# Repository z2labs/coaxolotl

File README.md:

# Coaxolotl

**A mast-head LNA and 8-way filter bank that lives entirely on one coax.**
An RTL-SDR's bias-T powers it, and the same bias-T switches it by blinking
its power in short gaps. It answers on the same coax with a keyed clock the
dongle receives, so the host sees what it did and what it measures. Its
front panel shows every internal state on a lamp, like a 1970s
minicomputer.

```
  BANK   ○THRU ○LF ○160/80 ○60-30 ○20-10 ○6/4m ●2m/AIR ○70/23cm
  FRAME  S:●○●  P:●●○●○○  C:○○●○●●
  DECODE ○RX ○0 ○1 ●OK ○ERR  | ○SYNC ○CHK ○GAP ○RUNT ○TMO
  RF     ●LNA ○BYP ○AUTO ●FMN  | ○I-LO ●I-OK ○I-HI ○TRIP
  SYSTEM ○RUN ●HOLD ○LOW ○QUIET  | ○DROP ○GLT ○RST
```

## How it works

```mermaid
flowchart LR
  PC[host<br/>coaxolotl.py · SDR++] -- USB --> RTL[RTL-SDR V3<br/>bias-T 4.5 V]
  RTL <== "RF + replies ↑ · DC + OOK gaps ↓" ==> BOX
  subgraph BOX[Coaxolotl box]
    direction TB
    DEC[EFM8BB2<br/>gap decoder] --> SW[LNA / bypass<br/>8x filter bank]
    DEC --> PANEL[48+1 lamps]
    SCAP[0.1 F hold-up] -.-> DEC
  end
  ANT[antenna] --> BOX
```

* **Link.** Bias off for 30 ms is a 0 and for 70 ms is a 1, with 100 ms of
  power between bits. A frame is `sync 101 | bank·LNA·quiet·clr | inverse`
  and takes about 2.5 s. The sync bits calibrate the threshold, so clock
  skew, slow discharge and USB jitter cancel out.
  → [docs/protocol.md](docs/protocol.md)
* **Back-channel.** After every frame (and once after boot) the MCU keys a
  12.25 MHz clock onto the coax for 0.8 s. The dongle hears its 3rd
  harmonic at 36.75 MHz. The 8-byte Manchester packet carries ACK/NAK with
  the error, the switch state actually set, VCOAX, the whole coax current
  (the bias-T budget, BUDGET flag at 170 mA), LNA current, supercap voltage
  and the sticky flags. Readings are calibrated against a meter over the same
  link. The host searches the band for it, so the ±2 % RC oscillator needs no
  trimming.
  → [docs/protocol.md](docs/protocol.md#back-channel-box--host)
* **SDR++.** `sdrpp/coaxolotl_source` is an RTL-SDR source for SDR++ with
  the link built in: branch, LNA, Send/Poll/Clear, follow-tuning and a
  telemetry readout. → [sdrpp/README.md](sdrpp/README.md)
* **RF path.** Antenna → protection → LNA (with preselector, optional FM
  notch) or bypass → PE42582 SP8T → 8 filters → PE42582 → bias-T → coax.
  The HF/LF branches force bypass automatically.
  → [bandplan.json](bandplan.json)
* **Power.**
  * An ideal diode keeps the sense node fast.
  * A 330 µF stage boots the MCU in about 30 ms, and a 0.1 F supercap rides
    through dropouts for minutes.
  * The LNA sits behind a current-limited switch with a shunt monitor.
  → [docs/hardware.md](docs/hardware.md)
* **Quiet when idle.** The EFM8BB2 Snoozes with its high-frequency clock
  stopped. It wakes only on a bias edge, an LNA fault or every 6.5 s for
  housekeeping. The lamps are statically latched, so there is no
  multiplexing noise either. The RUN lamp tells you when the MCU clock is
  running.
* **Panel.** 48 lamps on 6×74HC595 plus a hard-wired PWR lamp. It shows bank,
  received bits, decoder errors, LNA path and current, trip, hold-up, rail
  voltage and sticky dropout/glitch/reset flags. Software modes: full, bands
  only, or off (PWR lamp only), kept in flash. → [docs/panel.md](docs/panel.md)

## Quick start

```bash
# host tests + simulator (gcc, g++, python3 + numpy)
make -C firmware test sim
make -C sdrpp test
python3 -m unittest discover -s host

# what the box would do, without hardware
python3 host/coaxolotl.py send --band 2m --lna --backend dry-run \
  | firmware/build/sim --fall-delay 6 --jitter 2

# firmware (SDCC >= 4.2)
make -C firmware            # EFM8BB52 (control board), Snooze build
make -C firmware SNOOZE=0   # bring-up build, classic registers only
make -C firmware MCU=bb21   # EFM8BB21 QFN20: the 4-layer RF board

# real link
python3 host/coaxolotl.py bands
python3 host/coaxolotl.py send --band 2m --lna                 # pyrtlsdr
python3 host/coaxolotl.py send --bank 3 --backend rtl_biast    # rtl-sdr-blog tool
python3 host/coaxolotl.py panel bands                          # lamps: full | bands | off
python3 host/coaxolotl.py send --band 2m --lna --listen        # ... and read the reply
python3 host/coaxolotl_gui.py                                  # control panel (--sim: no hardware)
```

## Pin map

### EFM8BB52F32I-C-QFN32: control board (`make -C firmware`, the default)

Source of truth: `firmware/src/hal_efm8bb52.c`; checked against the
`hardware/kicad_ctrl` netlist.

| Pin | Port | Net | Dir | Function |
|---|---|---|---|---|
| 1 | P0.0 | VREF | ana | precision reference 2.4 V, C50 100 nF; on only while measuring |
| 32 | P0.1 | FAULT_N | in | TPS2553 FAULT, 100 k pull-up; port-match wake |
| 31 | P0.2 | SENSE | in + ana | VCOAX divider 11k/22k: port-match wake on both edges and ADC0.0 at once (PRTDRV.COEX); C2 10 nF |
| 30 | P0.3 | SCAP_ADC | ana | supercap / 2 (1 M / 1 M, C11), ADC0.1 |
| 29 | P0.4 | TP_TX | out | UART0 TX test point (factory bootloader, debug) |
| 28 | P0.5 | TP_RX | in | UART0 RX test point |
| 27 | P0.6 | LNA_EN | out | TPS2553 EN; 10 k pull-down |
| 26 | P0.7 | LNA_PATH | out | input SPDT U6, 1 = LNA; 10 k pull-down = bypass |
| 25, 24, 23 | P1.0–P1.2 | SW_V1..V3 | out | both PE42582 (via J6); 10 k pull-downs = F0 THRU |
| 22 | P1.3 | LNA_PATH_OUT | out | output SPDT U7, same polarity; 10 k pull-down |
| 21 | P1.4 | FMN | out | FM notch SPDTs; 10 k pull-down |
| 20, 19 | P1.5, P1.6 | — | out | spare, driven low |
| 18 | P1.7 | BEACON | out | PCA CEX0 12.25 MHz during a reply → R31/R32/R33/C47 → coax; low otherwise |
| 17 | P2.0 | LED_SER | out | 74HC595 chain data (U14 first) |
| 16 | P2.1 | LED_SCK | out | shift clock |
| 15 | P2.2 | LED_RCK | out | latch clock |
| 14 | P2.3 | LED_OE_N | out | output enable; 10 k pull-up = lamps dark in reset |
| 13 | P2.4 | ILNA_ADC | ana | LNA current: R7 0.39 Ω, U3 INA180A2, 19.5 mV/mA, R8/C7; ADC0.13 |
| 12 | P2.5 | ITOT_ADC | ana | whole coax current: R35 0.1 Ω, U20 INA180A3, 10 mV/mA, R36/C48; ADC0.14 |
| 11 | P2.6 | — | out | spare, driven low |
| 10–6 | P3.0–P3.4 | — | out | spare, driven low |
| 5 | P3.7 / C2D | C2D | | debug; R34 10 k pull-up (low at reset = factory bootloader) |
| 4 | RSTb / C2CK | RST_N | | R13 10 k pull-up, C2 clock |
| 3 | VDD | +3V3 | | C15 100 nF + C14 1 µF |
| 2 | N/C | | | |
| EP | GND | | | the only ground pin |

J6 (via row to a later RF board): 1 +3V3, 2 LNA_VCC, 3–5 SW_V1..V3,
6 LNA_PATH, 7 LNA_PATH_OUT, 8 FMN, 9–10 GND.

### EFM8BB21F16G-C-QFN20: 4-layer RF board (`make -C firmware MCU=bb21`)

Source of truth: `firmware/src/hal_efm8bb2.c`. All 16 port pins are used.

| Pin | Port | Net | Dir | Function |
|---|---|---|---|---|
| 2 | P0.0 | SENSE | in | VCOAX divider; port-match wake |
| 1 | P0.1 | VC_ADC | ana | same divider node |
| 20 | P0.2 | SCAP_ADC | ana | supercap / 2 |
| 19 | P0.3 | ILNA_ADC | ana | INA180A2 output |
| 18 | P0.4 | LED_OE_N | out | lamp output enable; 10 k pull-up |
| 17 | P0.5 | FAULT_N | in | TPS2553 FAULT; port-match wake |
| 16 | P0.6 | LNA_EN | out | 10 k pull-down |
| 15 | P0.7 | LNA_PATH | out | input SPDT U6; 10 k pull-down |
| 14, 13, 11 | P1.0–P1.2 | SW_V1..V3 | out | both PE42582; 10 k pull-downs |
| 10 | P1.3 | LNA_PATH_OUT | out | output SPDT U7; 10 k pull-down |
| 9 | P1.4 | LED_SER (+ BEACON) | out | 595 data; PCA CEX0 during a reply (no tap on this board yet) |
| 8 | P1.5 | LED_SCK | out | |
| 7 | P1.6 | LED_RCK | out | |
| 6 | P2.0 / C2D | FMN | out | through R30 1 k; 10 k pull-down |
| 5 | RSTb / C2CK | RST_N | | 10 k pull-up |
| 4 | VDD | +3V3 | | |
| 3, 12, EP | GND | | | |

No whole-coax current monitor on this board: I_TOT reads 0.

## Repository

| Path | What |
|---|---|
| `bandplan.json` | the 8 branches, single source of truth (firmware header is generated) |
| `firmware/src/decoder.*` | gap-width OOK decoder, pure C |
| `firmware/src/app.*` | RF routing, health, sticky flags, animations, pure C |
| `firmware/src/panel.*` | state → 48-bit lamp image |
| `firmware/src/beacon.*` | reply packet, CRC and chip sequence, pure C |
| `firmware/src/hal_efm8bb2.c`, `main.c` | EFM8BB21 (QFN20) hardware layer and main loop |
| `firmware/src/hal_efm8bb52.c` | EFM8BB52F32 (QFN32) hardware layer, the default build |
| `firmware/include/efm8bb*_sfr.h` | minimal SDCC SFR maps (BB2, BB52) |
| `firmware/test/` | unit tests and `sim` (edge replay + ASCII panel) |
| `host/coaxolotl.py` | keyer: pyrtlsdr / rtl_biast / dry-run, `--listen`, `listen`, `decode` |
| `host/backchannel.py` | reply packet and demodulator (numpy) |
| `host/link.py` | one open RTL-SDR (or the firmware simulator): key a frame, read the reply |
| `host/coaxolotl_gui.py` | control panel for the PC (tkinter), see `docs/host.md` |
| `sdrpp/` | SDR++ source module and its standalone tests |
| `hardware/kicad/` | 4-layer RF board: generated schematic (`tools/build.py`), layout, JLC package in `jlc/` |
| `hardware/kicad_ctrl/` | 2-layer control board without RF (`COAX_VARIANT=ctrl`), JLC package in `jlc/` |
| `hardware/bom.csv` | grouped BOM of the RF board schematic (`tools/bom.py`) |
| `docs/` | protocol, hardware, panel, bring-up, PC software (`host.md`) |

## Status (v0.1)

* ✅ Decoder, app logic and panel pass 194 host checks. That includes all 64
  payloads, 1800 randomised frames at ±10 % clock skew, 0–10 ms fall delay
  and ±3 ms jitter, every error path and the LED power budget.
* ✅ Host encoder → firmware decoder, end to end, through the simulator.
* ✅ The firmware builds with SDCC 4.2, back-channel included, in both the
  Snooze and the bring-up build: EFM8BB52F32 about 15.4 of 28 kB, EFM8BB21F16G
  about 15.2 of 15.4 kB (full: new features go to the BB52 only). One flash
  page holds the settings log (panel mode, calibration).
* ✅ PC control panel (`host/coaxolotl_gui.py`) and link layer (`host/link.py`),
  tested end to end against the firmware simulator.
* ✅ Back-channel: firmware checks for HELLO/ACK/NAK, timing, contents and
  the chip round-trip. Firmware packets go through the simulator into the
  Python and C++ demodulators, which decode synthetic captures with the
  carrier anywhere in ±0.75 MHz and chips ±10 %.
* ⚠️ The SDR++ module compiles against the SDR++ headers but has not run in
  SDR++ yet. The beacon level (about −65 dBm) is calculated, not measured.
* ⚠️ The firmware has **not run on silicon yet**. Three EFM8BB2 register
  details (Snooze bit, Timer 4 LFOSC clock select, Snooze wake on a Timer 4
  wrap), the ADC setup and the PCA/CLKSEL/crossbar setup of the beacon are
  marked VERIFY. `docs/bringup.md` has a test
  for each, and the `SNOOZE=0` build avoids them.
* ✅ Schematic and two routed layouts with JLC packages: the 4-layer RF board
  (`hardware/kicad`) and the 2-layer control board without RF
  (`hardware/kicad_ctrl`). Open items are listed in `docs/hardware.md`.

## License

| Part | License |
|---|---|
| Hardware: `hardware/` (schematics, PCB, BOM), and the hardware design in `docs/hardware.md` | [CERN-OHL-S-2.0](hardware/LICENSE) |
| Software: `firmware/`, `host/`, `tools/`, future SDR plugins | [MIT](LICENSE) |

Documentation follows the part it describes.

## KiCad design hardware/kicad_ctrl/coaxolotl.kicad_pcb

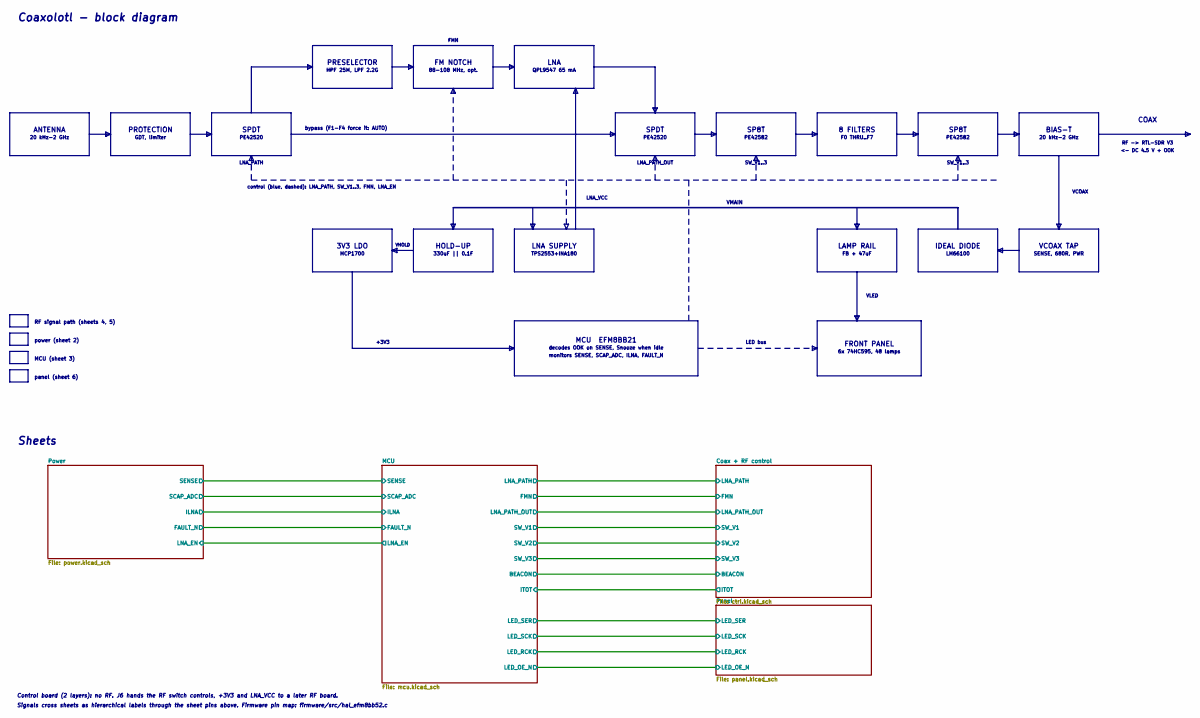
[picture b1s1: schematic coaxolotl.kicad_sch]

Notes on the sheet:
Coaxolotl - block diagram
ANTENNA
20 kHz-2 GHz
PROTECTION
GDT, limiter
SPDT
PE42520
SP8T
PE42582
8 FILTERS
F0 THRU..F7
BIAS-T
PRESELECTOR
HPF 25M, LPF 2.2G
FM NOTCH
88-108 MHz, opt.
LNA
QPL9547 65 mA
bypass (F1-F4 force it: AUTO)
COAX
RF -> RTL-SDR V3
<- DC 4.5 V + OOK
LNA_PATH
LNA_PATH_OUT
SW_V1..3
FMN
VCOAX TAP
SENSE, 680R, PWR
IDEAL DIODE
LM66100
LAMP RAIL
FB + 47uF
LNA SUPPLY
TPS2553+INA180
HOLD-UP
330uF || 0.1F
3V3 LDO
MCP1700
VCOAX
VMAIN

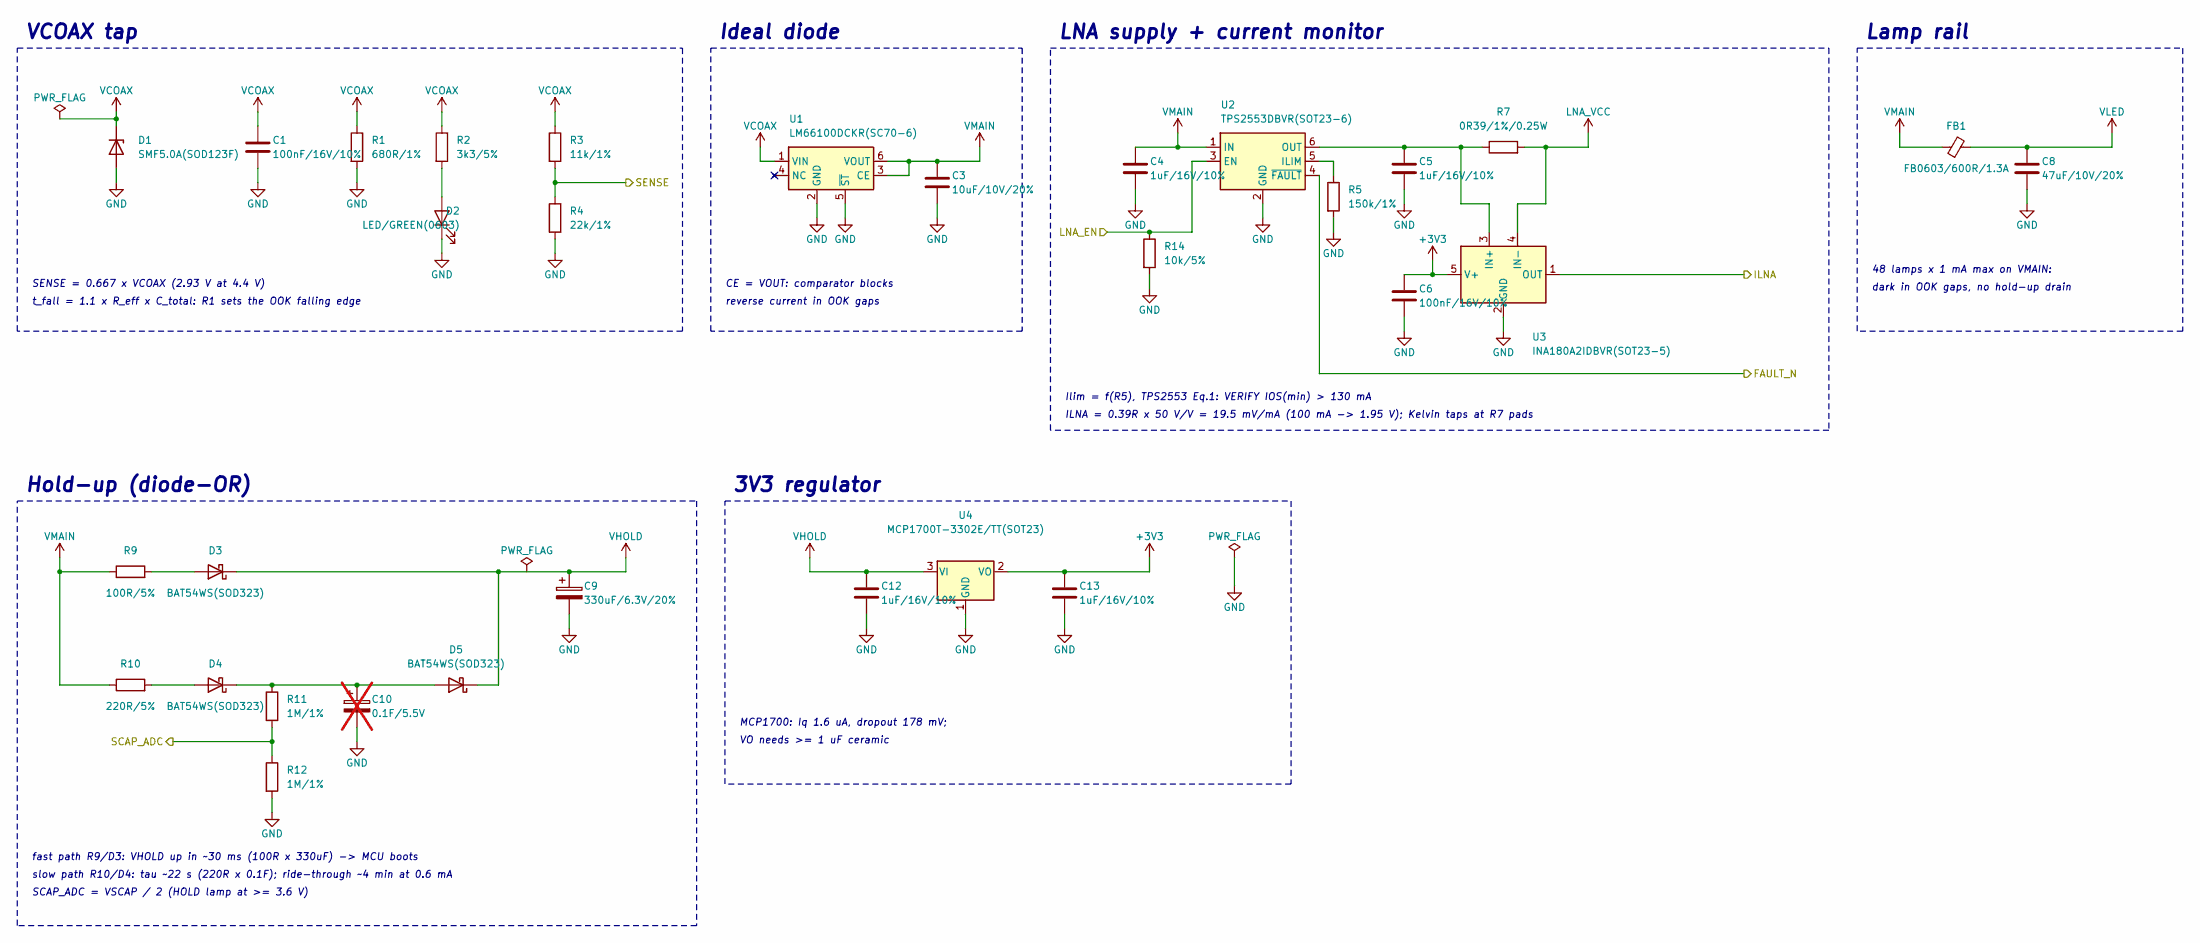
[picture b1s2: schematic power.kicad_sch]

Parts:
C1, C6: 100nF/16V/10%; C_0603_1608Metric
C3: 10uF/10V/20%; C_0805_2012Metric
C4, C5, C12, C13: 1uF/16V/10%; C_0603_1608Metric
C8: 47uF/10V/20%; C_1206_3216Metric
C9: 330uF/6.3V/20%; CP_EIA-7343-31_Kemet-D; MPN T520D337M006ATE025
C10: 0.1F/5.5V; CP_Radial_D13.0mm_P5.00mm; MPN KR-5R5V104-R; not fitted
D1: SMF5.0A(SOD123F); D_SOD-123F
D2: LED/GREEN(0603); LED_0603_1608Metric
D3, D4, D5: BAT54WS(SOD323); D_SOD-323
FB1: FB0603/600R/1.3A; L_0603_1608Metric; MPN BLM18KG601SN1D
R1: 680R/1%; R_0603_1608Metric
R2: 3k3/5%; R_0603_1608Metric
R3: 11k/1%; R_0603_1608Metric
R4: 22k/1%; R_0603_1608Metric
R5: 150k/1%; R_0603_1608Metric
R7: 0R39/1%/0.25W; R_1206_3216Metric; MPN ERJ-8BQFR39V
R9: 100R/5%; R_0603_1608Metric
R10: 220R/5%; R_0603_1608Metric
R11, R12: 1M/1%; R_0603_1608Metric
R14: 10k/5%; R_0603_1608Metric
U1: LM66100DCKR(SC70-6); SOT-363_SC-70-6
U2: TPS2553DBVR(SOT23-6); SOT-23-6
U3: INA180A2IDBVR(SOT23-5); SOT-23-5
U4: MCP1700T-3302E/TT(SOT23); SOT-23

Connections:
+3V3: C6.1, C13.1, U3.5 (V+), U4.2 (VO); also elsewhere on the board
/MCU/FAULT_N: U2.4 (~FAULT); also elsewhere on the board
/MCU/ILNA: U3.1 (OUT); also elsewhere on the board
/MCU/LNA_EN: R14.1, U2.3 (EN); also elsewhere on the board
/MCU/SCAP_ADC: R11.2, R12.1; also elsewhere on the board
/MCU/SENSE: R3.2, R4.1; also elsewhere on the board
GND: C1.2, C3.2, C4.2, C5.2, C6.2, C8.2, C9.2, C10.2, C12.2, C13.2, D1.2 (A), D2.1 (K), R1.2, R4.2, R5.2, R12.2, R14.2, U1.2 (GND), U1.5 (~ST), U2.2 (GND), U3.2 (GND), U4.1 (GND); also elsewhere on the board
LNA_VCC: R7.2, U3.4 (IN-); also elsewhere on the board
unnamed: D2.2 (A), R2.2
unnamed: D3.2 (A), R9.2
unnamed: D4.2 (A), R10.2
unnamed: C10.1, D4.1 (K), D5.2 (A), R11.1
unnamed: R5.1, U2.5 (ILIM)
unnamed: C5.1, R7.1, U2.6 (OUT), U3.3 (IN+)
VCOAX: C1.1, D1.1 (K), R1.1, R2.1, R3.1, U1.1 (VIN); also elsewhere on the board
VHOLD: C9.1, C12.1, D3.1 (K), D5.1 (K), U4.3 (VI)
VLED: C8.1, FB1.2; also elsewhere on the board
VMAIN: C3.1, C4.1, FB1.1, R9.1, R10.1, U1.3 (CE), U1.6 (VOUT), U2.1 (IN)

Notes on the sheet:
VCOAX tap
SENSE = 0.667 x VCOAX (2.93 V at 4.4 V)
t_fall = 1.1 x R_eff x C_total: R1 sets the OOK falling edge
Ideal diode
CE = VOUT: comparator blocks
reverse current in OOK gaps
LNA supply + current monitor
Ilim = f(R5), TPS2553 Eq.1: VERIFY IOS(min) > 130 mA
ILNA = 0.39R x 50 V/V = 19.5 mV/mA (100 mA -> 1.95 V); Kelvin taps at R7 pads
Lamp rail
48 lamps x 1 mA max on VMAIN:
dark in OOK gaps, no hold-up drain
Hold-up (diode-OR)
fast path R9/D3: VHOLD up in ~30 ms (100R x 330uF) -> MCU boots
slow path R10/D4: tau ~22 s (220R x 0.1F); ride-through ~4 min at 0.6 mA
SCAP_ADC = VSCAP / 2 (HOLD lamp at >= 3.6 V)
3V3 regulator
MCP1700: Iq 1.6 uA, dropout 178 mV;
VO needs >= 1 uF ceramic

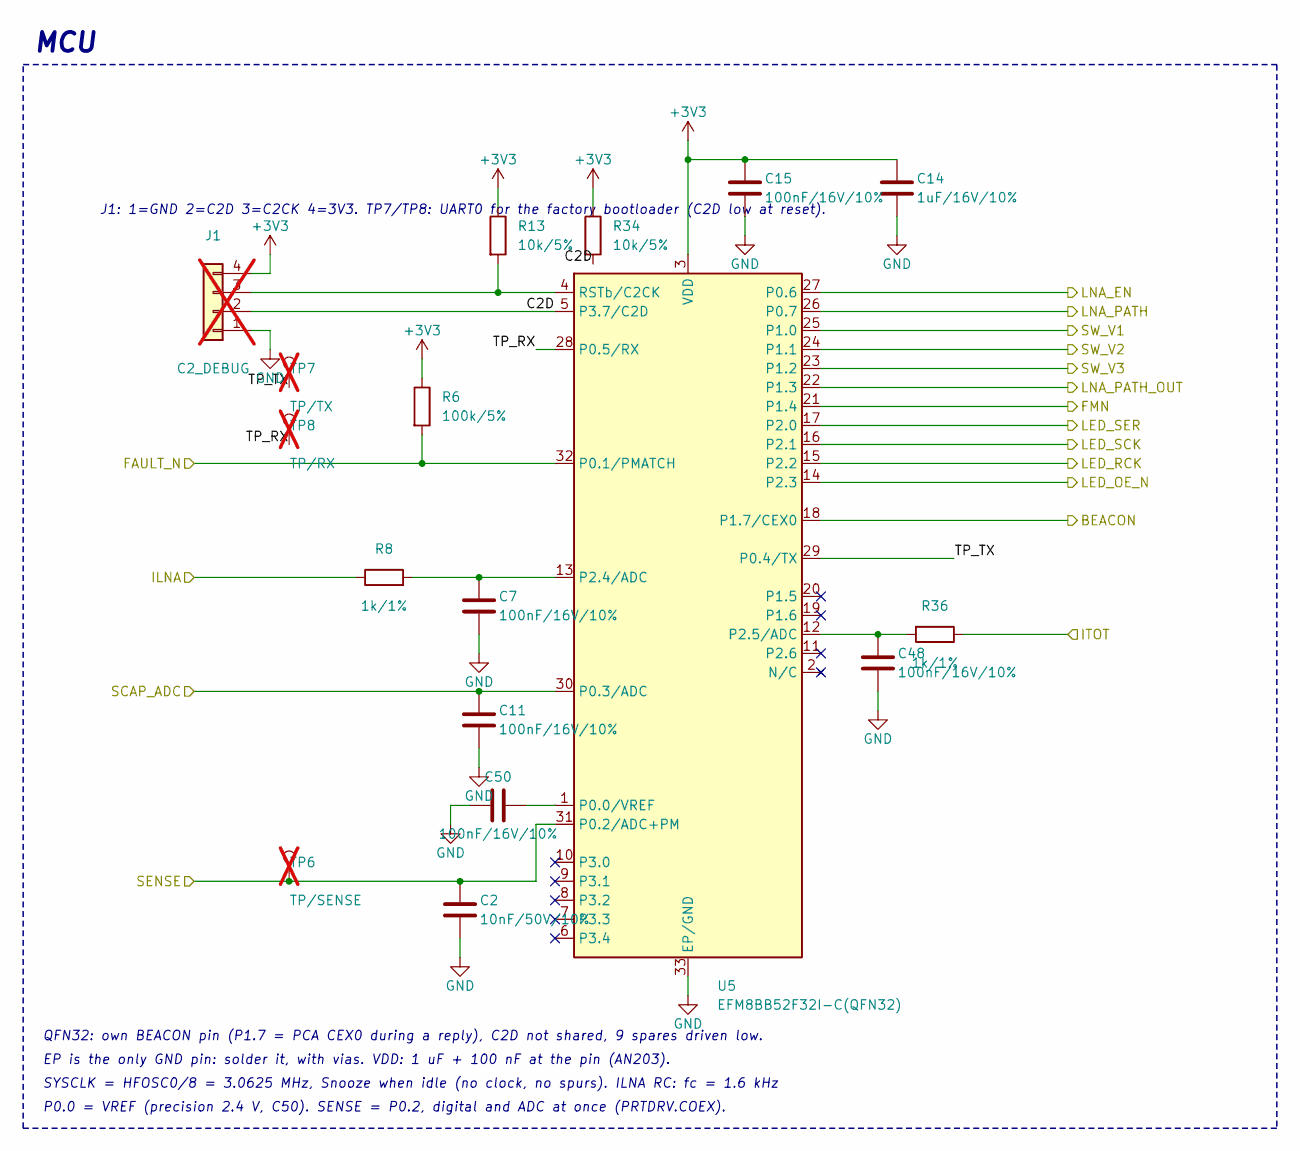
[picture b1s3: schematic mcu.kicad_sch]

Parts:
C2: 10nF/50V/10%; C_0603_1608Metric
C7, C11, C15, C48, C50: 100nF/16V/10%; C_0603_1608Metric
C14: 1uF/16V/10%; C_0603_1608Metric
J1: C2_DEBUG; PinHeader_1x04_P2.54mm_Vertical; not fitted
R6: 100k/5%; R_0603_1608Metric
R8, R36: 1k/1%; R_0603_1608Metric
R13, R34: 10k/5%; R_0603_1608Metric
TP6: TP/SENSE; TestPoint_Pad_D1.0mm; not fitted
TP7: TP/TX; TestPoint_Pad_D1.0mm; not fitted
TP8: TP/RX; TestPoint_Pad_D1.0mm; not fitted
U5: EFM8BB52F32I-C(QFN32); QFN-32-1EP_5x5mm_P0.5mm_EP3.45x3.45mm

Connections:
+3V3: C14.1, C15.1, J1.4, R6.1, R13.1, R34.1, U5.3 (VDD); also elsewhere on the board
/Coax + RF control/BEACON: U5.18 (P1.7/CEX0); also elsewhere on the board
/Coax + RF control/FMN: U5.21 (P1.4); also elsewhere on the board
/Coax + RF control/ITOT: R36.1; also elsewhere on the board
/Coax + RF control/LNA_PATH: U5.26 (P0.7); also elsewhere on the board
/Coax + RF control/LNA_PATH_OUT: U5.22 (P1.3); also elsewhere on the board
/Coax + RF control/SW_V1: U5.25 (P1.0); also elsewhere on the board
/Coax + RF control/SW_V2: U5.24 (P1.1); also elsewhere on the board
/Coax + RF control/SW_V3: U5.23 (P1.2); also elsewhere on the board
/MCU/C2D: J1.2, R34.2, U5.5 (P3.7/C2D)
/MCU/FAULT_N: R6.2, U5.32 (P0.1/PMATCH); also elsewhere on the board
/MCU/ILNA: R8.1; also elsewhere on the board
/MCU/LED_OE_N: U5.14 (P2.3); also elsewhere on the board
/MCU/LED_RCK: U5.15 (P2.2); also elsewhere on the board
/MCU/LED_SCK: U5.16 (P2.1); also elsewhere on the board
/MCU/LED_SER: U5.17 (P2.0); also elsewhere on the board
/MCU/LNA_EN: U5.27 (P0.6); also elsewhere on the board
/MCU/SCAP_ADC: C11.1, U5.30 (P0.3/ADC); also elsewhere on the board
/MCU/SENSE: C2.1, TP6.1, U5.31 (P0.2/ADC+PM); also elsewhere on the board
/MCU/TP_RX: TP8.1, U5.28 (P0.5/RX)
/MCU/TP_TX: TP7.1, U5.29 (P0.4/TX)
GND: C2.2, C7.2, C11.2, C14.2, C15.2, C48.2, C50.1, J1.1, U5.33 (EP/GND); also elsewhere on the board
unnamed: J1.3, R13.2, U5.4 (RSTb/C2CK)
unnamed: C50.2, U5.1 (P0.0/VREF)
unnamed: C7.1, R8.2, U5.13 (P2.4/ADC)
unnamed: C48.1, R36.2, U5.12 (P2.5/ADC)

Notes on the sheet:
MCU
J1: 1=GND 2=C2D 3=C2CK 4=3V3. TP7/TP8: UART0 for the factory bootloader (C2D low at reset).
QFN32: own BEACON pin (P1.7 = PCA CEX0 during a reply), C2D not shared, 9 spares driven low.
P0.0 = VREF (precision 2.4 V, C50). SENSE = P0.2, digital and ADC at once (PRTDRV.COEX).
EP is the only GND pin: solder it, with vias. VDD: 1 uF + 100 nF at the pin (AN203).
SYSCLK = HFOSC0/8 = 3.0625 MHz, Snooze when idle (no clock, no spurs). ILNA RC: fc = 1.6 kHz

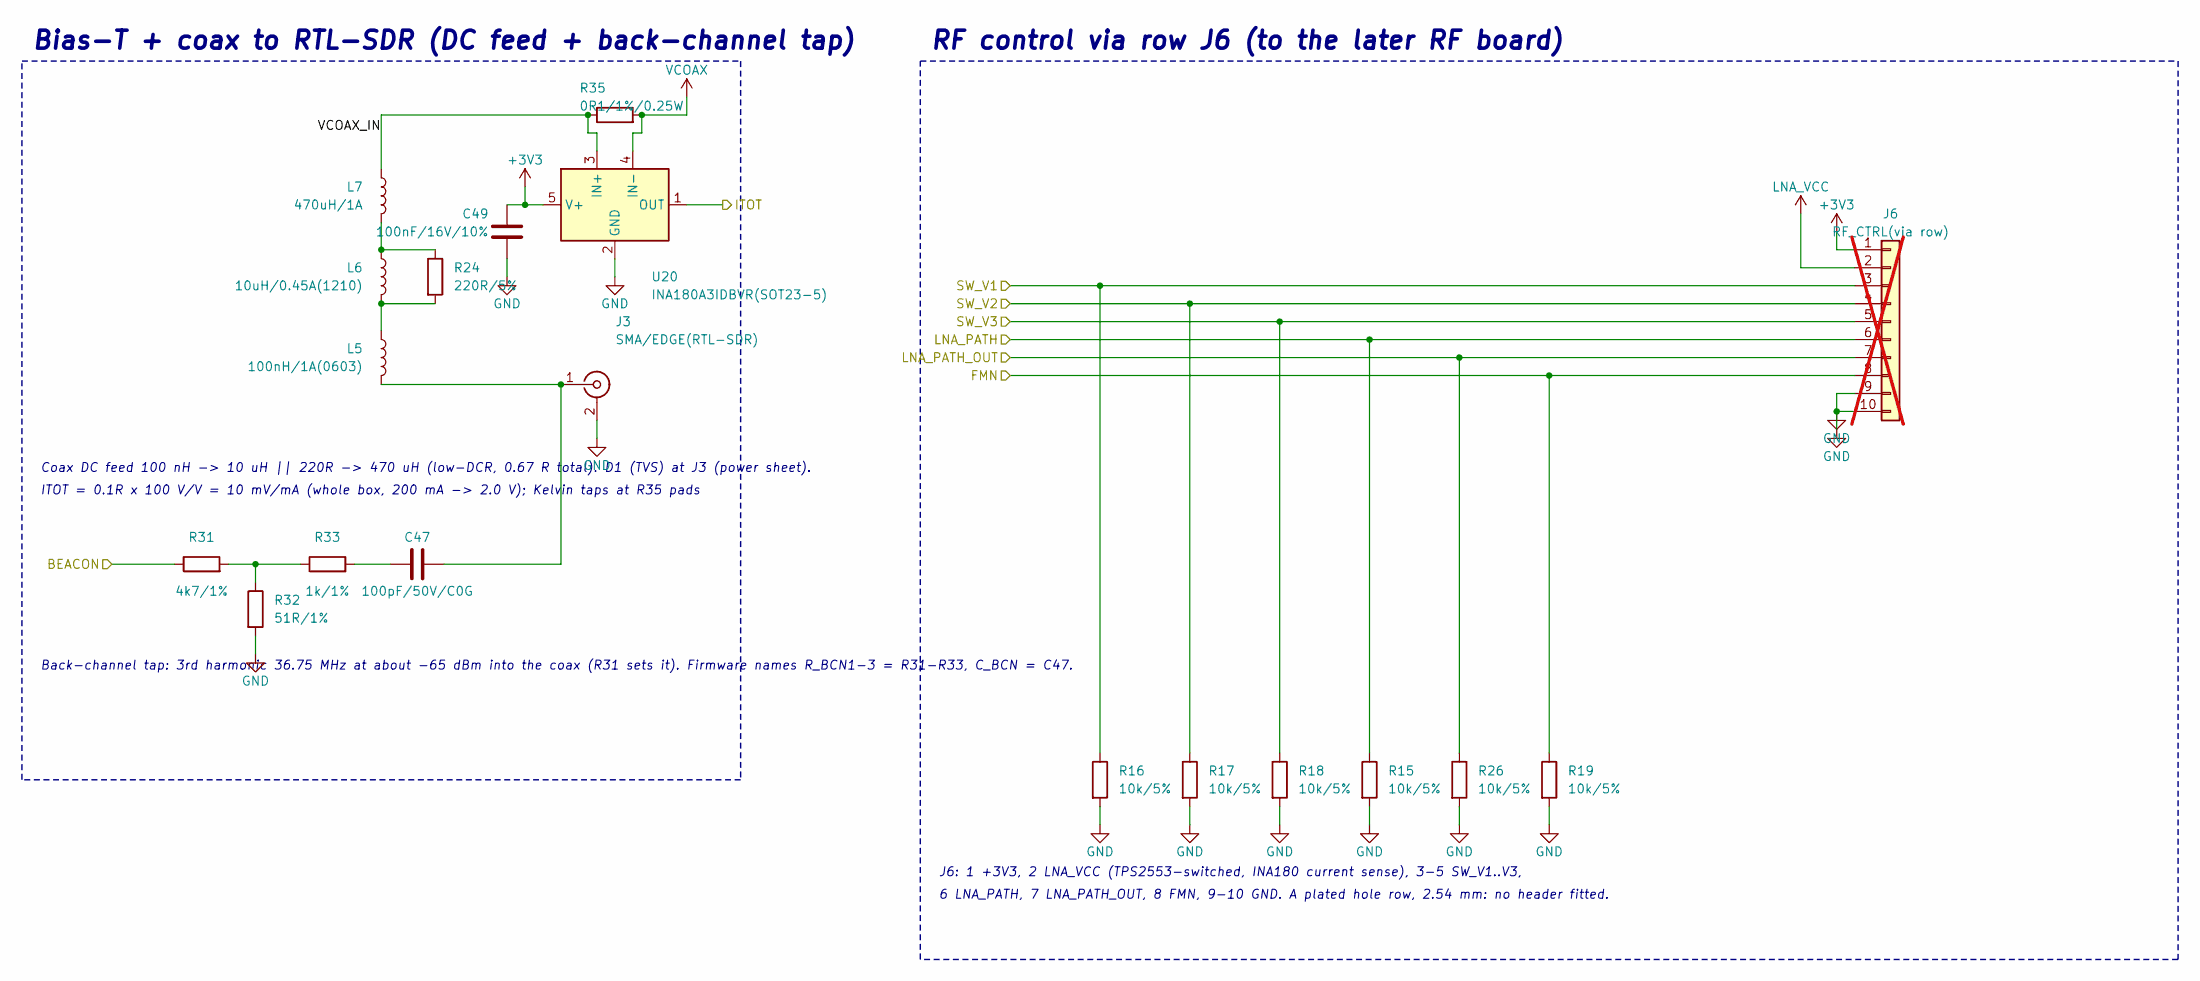
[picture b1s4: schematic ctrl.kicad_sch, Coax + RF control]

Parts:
C47: 100pF/50V/C0G; C_0603_1608Metric
C49: 100nF/16V/10%; C_0603_1608Metric
J3: SMA/EDGE(RTL-SDR); SMA_EdgeLaunch_BWSMA-KE-P001_Air
J6: RF_CTRL(via row); PinHeader_1x10_P2.54mm_Vertical; not fitted
L5: 100nH/1A(0603); L_0603_1608Metric; MPN LQW18CNR10K0ZD
L6: 10uH/0.45A(1210); L_1210_3225Metric; MPN LQH32CN100K33L
L7: 470uH/1A; L_YJYCOIN_YPRH1209; MPN YPRH1209-471M
R15, R16, R17, R18, R19, R26: 10k/5%; R_0603_1608Metric
R24: 220R/5%; R_0603_1608Metric
R31: 4k7/1%; R_0603_1608Metric
R32: 51R/1%; R_0603_1608Metric
R33: 1k/1%; R_0603_1608Metric
R35: 0R1/1%/0.25W; R_1206_3216Metric
U20: INA180A3IDBVR(SOT23-5); SOT-23-5

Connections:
+3V3: C49.1, J6.1, U20.5 (V+); also elsewhere on the board
/Coax + RF control/BEACON: R31.1; also elsewhere on the board
/Coax + RF control/FMN: J6.8, R19.1; also elsewhere on the board
/Coax + RF control/ITOT: U20.1 (OUT); also elsewhere on the board
/Coax + RF control/LNA_PATH: J6.6, R15.1; also elsewhere on the board
/Coax + RF control/LNA_PATH_OUT: J6.7, R26.1; also elsewhere on the board
/Coax + RF control/SW_V1: J6.3, R16.1; also elsewhere on the board
/Coax + RF control/SW_V2: J6.4, R17.1; also elsewhere on the board
/Coax + RF control/SW_V3: J6.5, R18.1; also elsewhere on the board
/Coax + RF control/VCOAX_IN: L7.1, R35.1, U20.3 (IN+)
GND: C49.2, J3.2 (Ext), J6.9, J6.10, R15.2, R16.2, R17.2, R18.2, R19.2, R26.2, R32.2, U20.2 (GND); also elsewhere on the board
LNA_VCC: J6.2; also elsewhere on the board
unnamed: C47.1, R33.2
unnamed: C47.2, J3.1 (In), L5.2
unnamed: L5.1, L6.2, R24.2
unnamed: L6.1, L7.2, R24.1
unnamed: R31.2, R32.1, R33.1
VCOAX: R35.2, U20.4 (IN-); also elsewhere on the board

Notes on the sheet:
Bias-T + coax to RTL-SDR (DC feed + back-channel tap)
Coax DC feed 100 nH -> 10 uH || 220R -> 470 uH (low-DCR, 0.67 R total). D1 (TVS) at J3 (power sheet).
ITOT = 0.1R x 100 V/V = 10 mV/mA (whole box, 200 mA -> 2.0 V); Kelvin taps at R35 pads
Back-channel tap: 3rd harmonic 36.75 MHz at about -65 dBm into the coax (R31 sets it). Firmware names R_BCN1-3 = R31-R33, C_BCN = C47.
RF control via row J6 (to the later RF board)
J6: 1 +3V3, 2 LNA_VCC (TPS2553-switched, INA180 current sense), 3-5 SW_V1..V3,
6 LNA_PATH, 7 LNA_PATH_OUT, 8 FMN, 9-10 GND. A plated hole row, 2.54 mm: no header fitted.

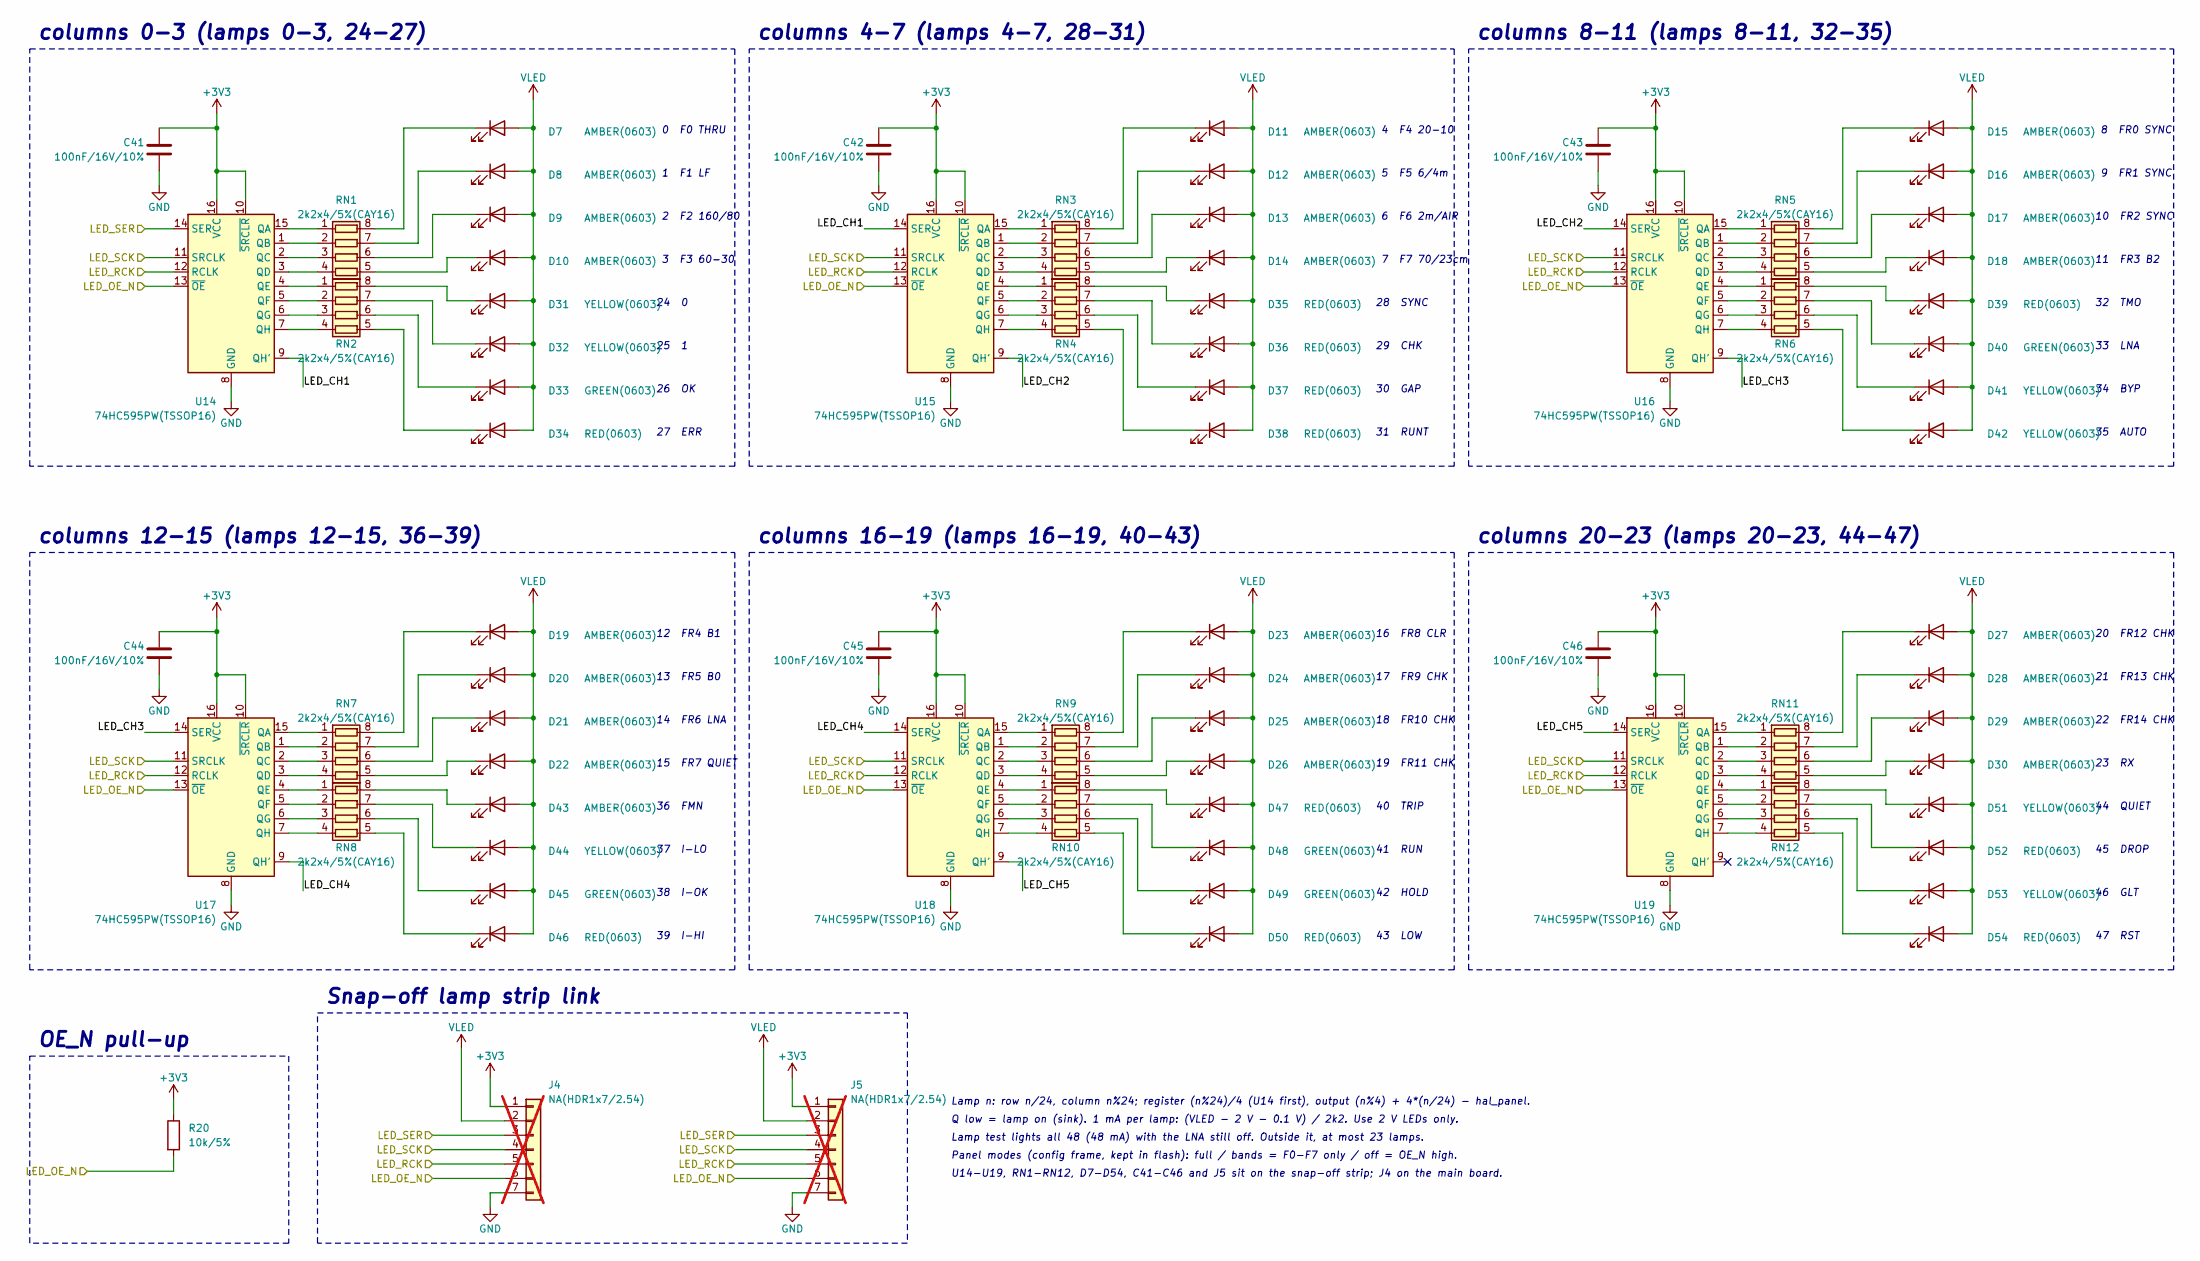
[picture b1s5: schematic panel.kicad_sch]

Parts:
C41, C42, C43, C44, C45, C46: 100nF/16V/10%; C_0603_1608Metric
D7, D8, D9, D10, D11, D12, D13, D14, D15, D16, D17, D18, D19, D20, D21, D22, D23, D24, D25, D26, D27, D28, D29, D30, D43: AMBER(0603); LED_0603_1608Metric
D31, D32, D41, D42, D44, D51, D53: YELLOW(0603); LED_0603_1608Metric
D33, D40, D45, D48, D49: GREEN(0603); LED_0603_1608Metric
D34, D35, D36, D37, D38, D39, D46, D47, D50, D52, D54: RED(0603); LED_0603_1608Metric
J4, J5: NA(HDR1x7/2.54); PinHeader_1x07_P2.54mm_Vertical; not fitted
R20: 10k/5%; R_0603_1608Metric
RN1, RN2, RN3, RN4, RN5, RN6, RN7, RN8, RN9, RN10, RN11, RN12: 2k2x4/5%(CAY16); R_Array_Convex_4x0603; MPN CAY16-222J4LF
U14, U15, U16, U17, U18, U19: 74HC595PW(TSSOP16); TSSOP-16_4.4x5mm_P0.65mm

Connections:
+3V3: C41.1, C42.1, C43.1, C44.1, C45.1, C46.1, J4.1, J5.1, R20.1, U14.10 (~SRCLR), U14.16 (VCC), U15.10 (~SRCLR), U15.16 (VCC), U16.10 (~SRCLR), U16.16 (VCC), U17.10 (~SRCLR), U17.16 (VCC), U18.10 (~SRCLR), U18.16 (VCC), U19.10 (~SRCLR), U19.16 (VCC); also elsewhere on the board
/MCU/LED_OE_N: J4.6, J5.6, R20.2, U14.13 (~OE), U15.13 (~OE), U16.13 (~OE), U17.13 (~OE), U18.13 (~OE), U19.13 (~OE); also elsewhere on the board
/MCU/LED_RCK: J4.5, J5.5, U14.12 (RCLK), U15.12 (RCLK), U16.12 (RCLK), U17.12 (RCLK), U18.12 (RCLK), U19.12 (RCLK); also elsewhere on the board
/MCU/LED_SCK: J4.4, J5.4, U14.11 (SRCLK), U15.11 (SRCLK), U16.11 (SRCLK), U17.11 (SRCLK), U18.11 (SRCLK), U19.11 (SRCLK); also elsewhere on the board
/MCU/LED_SER: J4.3, J5.3, U14.14 (SER); also elsewhere on the board
/Panel/LED_CH1: U14.9 (QH'), U15.14 (SER)
/Panel/LED_CH2: U15.9 (QH'), U16.14 (SER)
/Panel/LED_CH3: U16.9 (QH'), U17.14 (SER)
/Panel/LED_CH4: U17.9 (QH'), U18.14 (SER)
/Panel/LED_CH5: U18.9 (QH'), U19.14 (SER)
GND: C41.2, C42.2, C43.2, C44.2, C45.2, C46.2, J4.7, J5.7, U14.8 (GND), U15.8 (GND), U16.8 (GND), U17.8 (GND), U18.8 (GND), U19.8 (GND); also elsewhere on the board
unnamed: D7.1 (K), RN1.8 (R1.2)
unnamed: D8.1 (K), RN1.7 (R2.2)
unnamed: D9.1 (K), RN1.6 (R3.2)
unnamed: D10.1 (K), RN1.5 (R4.2)
unnamed: D11.1 (K), RN3.8 (R1.2)
unnamed: D12.1 (K), RN3.7 (R2.2)
unnamed: D13.1 (K), RN3.6 (R3.2)
unnamed: D14.1 (K), RN3.5 (R4.2)
unnamed: D15.1 (K), RN5.8 (R1.2)
unnamed: D16.1 (K), RN5.7 (R2.2)
unnamed: D17.1 (K), RN5.6 (R3.2)
unnamed: D18.1 (K), RN5.5 (R4.2)
unnamed: D19.1 (K), RN7.8 (R1.2)
unnamed: D20.1 (K), RN7.7 (R2.2)
unnamed: D21.1 (K), RN7.6 (R3.2)
unnamed: D22.1 (K), RN7.5 (R4.2)
unnamed: D23.1 (K), RN9.8 (R1.2)
unnamed: D24.1 (K), RN9.7 (R2.2)
unnamed: D25.1 (K), RN9.6 (R3.2)
unnamed: D26.1 (K), RN9.5 (R4.2)
unnamed: D27.1 (K), RN11.8 (R1.2)
unnamed: D28.1 (K), RN11.7 (R2.2)
unnamed: D29.1 (K), RN11.6 (R3.2)
unnamed: D30.1 (K), RN11.5 (R4.2)
unnamed: D31.1 (K), RN2.8 (R1.2)
unnamed: D32.1 (K), RN2.7 (R2.2)
unnamed: D33.1 (K), RN2.6 (R3.2)
unnamed: D34.1 (K), RN2.5 (R4.2)
unnamed: D35.1 (K), RN4.8 (R1.2)
unnamed: D36.1 (K), RN4.7 (R2.2)
unnamed: D37.1 (K), RN4.6 (R3.2)
unnamed: D38.1 (K), RN4.5 (R4.2)
unnamed: D39.1 (K), RN6.8 (R1.2)
unnamed: D40.1 (K), RN6.7 (R2.2)
unnamed: D41.1 (K), RN6.6 (R3.2)
unnamed: D42.1 (K), RN6.5 (R4.2)
unnamed: D43.1 (K), RN8.8 (R1.2)
unnamed: D44.1 (K), RN8.7 (R2.2)
unnamed: D45.1 (K), RN8.6 (R3.2)
unnamed: D46.1 (K), RN8.5 (R4.2)
unnamed: D47.1 (K), RN10.8 (R1.2)
unnamed: D48.1 (K), RN10.7 (R2.2)
unnamed: D49.1 (K), RN10.6 (R3.2)
unnamed: D50.1 (K), RN10.5 (R4.2)
unnamed: D51.1 (K), RN12.8 (R1.2)
unnamed: D52.1 (K), RN12.7 (R2.2)
unnamed: D53.1 (K), RN12.6 (R3.2)
unnamed: D54.1 (K), RN12.5 (R4.2)
unnamed: RN1.1 (R1.1), U14.15 (QA)
unnamed: RN1.2 (R2.1), U14.1 (QB)
unnamed: RN1.3 (R3.1), U14.2 (QC)
unnamed: RN1.4 (R4.1), U14.3 (QD)
unnamed: RN2.1 (R1.1), U14.4 (QE)
unnamed: RN2.2 (R2.1), U14.5 (QF)
unnamed: RN2.3 (R3.1), U14.6 (QG)
unnamed: RN2.4 (R4.1), U14.7 (QH)
unnamed: RN3.1 (R1.1), U15.15 (QA)
unnamed: RN3.2 (R2.1), U15.1 (QB)
unnamed: RN3.3 (R3.1), U15.2 (QC)
unnamed: RN3.4 (R4.1), U15.3 (QD)
unnamed: RN4.1 (R1.1), U15.4 (QE)
unnamed: RN4.2 (R2.1), U15.5 (QF)
unnamed: RN4.3 (R3.1), U15.6 (QG)
unnamed: RN4.4 (R4.1), U15.7 (QH)
unnamed: RN5.1 (R1.1), U16.15 (QA)
unnamed: RN5.2 (R2.1), U16.1 (QB)
unnamed: RN5.3 (R3.1), U16.2 (QC)
unnamed: RN5.4 (R4.1), U16.3 (QD)
unnamed: RN6.1 (R1.1), U16.4 (QE)
unnamed: RN6.2 (R2.1), U16.5 (QF)
unnamed: RN6.3 (R3.1), U16.6 (QG)
unnamed: RN6.4 (R4.1), U16.7 (QH)
unnamed: RN7.1 (R1.1), U17.15 (QA)
unnamed: RN7.2 (R2.1), U17.1 (QB)
unnamed: RN7.3 (R3.1), U17.2 (QC)
unnamed: RN7.4 (R4.1), U17.3 (QD)
unnamed: RN8.1 (R1.1), U17.4 (QE)
unnamed: RN8.2 (R2.1), U17.5 (QF)
unnamed: RN8.3 (R3.1), U17.6 (QG)
unnamed: RN8.4 (R4.1), U17.7 (QH)
unnamed: RN9.1 (R1.1), U18.15 (QA)
unnamed: RN9.2 (R2.1), U18.1 (QB)
unnamed: RN9.3 (R3.1), U18.2 (QC)
unnamed: RN9.4 (R4.1), U18.3 (QD)
unnamed: RN10.1 (R1.1), U18.4 (QE)
unnamed: RN10.2 (R2.1), U18.5 (QF)
unnamed: RN10.3 (R3.1), U18.6 (QG)
unnamed: RN10.4 (R4.1), U18.7 (QH)
unnamed: RN11.1 (R1.1), U19.15 (QA)
unnamed: RN11.2 (R2.1), U19.1 (QB)
unnamed: RN11.3 (R3.1), U19.2 (QC)
unnamed: RN11.4 (R4.1), U19.3 (QD)
unnamed: RN12.1 (R1.1), U19.4 (QE)
unnamed: RN12.2 (R2.1), U19.5 (QF)
unnamed: RN12.3 (R3.1), U19.6 (QG)
unnamed: RN12.4 (R4.1), U19.7 (QH)
VLED: D7.2 (A), D8.2 (A), D9.2 (A), D10.2 (A), D11.2 (A), D12.2 (A), D13.2 (A), D14.2 (A), D15.2 (A), D16.2 (A), D17.2 (A), D18.2 (A), D19.2 (A), D20.2 (A), D21.2 (A), D22.2 (A), D23.2 (A), D24.2 (A), D25.2 (A), D26.2 (A), D27.2 (A), D28.2 (A), D29.2 (A), D30.2 (A), D31.2 (A), D32.2 (A), D33.2 (A), D34.2 (A), D35.2 (A), D36.2 (A), D37.2 (A), D38.2 (A), D39.2 (A), D40.2 (A), D41.2 (A), D42.2 (A), D43.2 (A), D44.2 (A), D45.2 (A), D46.2 (A), D47.2 (A), D48.2 (A), D49.2 (A), D50.2 (A), D51.2 (A), D52.2 (A), D53.2 (A), D54.2 (A), J4.2, J5.2; also elsewhere on the board

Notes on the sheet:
columns 0-3 (lamps 0-3, 24-27)
0 F0 THRU
1 F1 LF
2 F2 160/80
3 F3 60-30
24 0
25 1
26 OK
27 ERR
columns 4-7 (lamps 4-7, 28-31)
4 F4 20-10
5 F5 6/4m
6 F6 2m/AIR
7 F7 70/23cm
28 SYNC
29 CHK
30 GAP
31 RUNT
columns 8-11 (lamps 8-11, 32-35)
8 FR0 SYNC
9 FR1 SYNC
10 FR2 SYNC
11 FR3 B2
32 TMO
33 LNA
34 BYP
35 AUTO
columns 12-15 (lamps 12-15, 36-39)
12 FR4 B1
13 FR5 B0
14 FR6 LNA
15 FR7 QUIET
36 FMN
37 I-LO
38 I-OK
39 I-HI
columns 16-19 (lamps 16-19, 40-43)
16 FR8 CLR
17 FR9 CHK
18 FR10 CHK
